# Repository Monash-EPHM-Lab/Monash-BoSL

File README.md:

# Monash-BoSL
Monash-BoSL project repository

This repostory contains all the hardware and software resources for the BoSL board.

Find our website at: www.bosl.com.au

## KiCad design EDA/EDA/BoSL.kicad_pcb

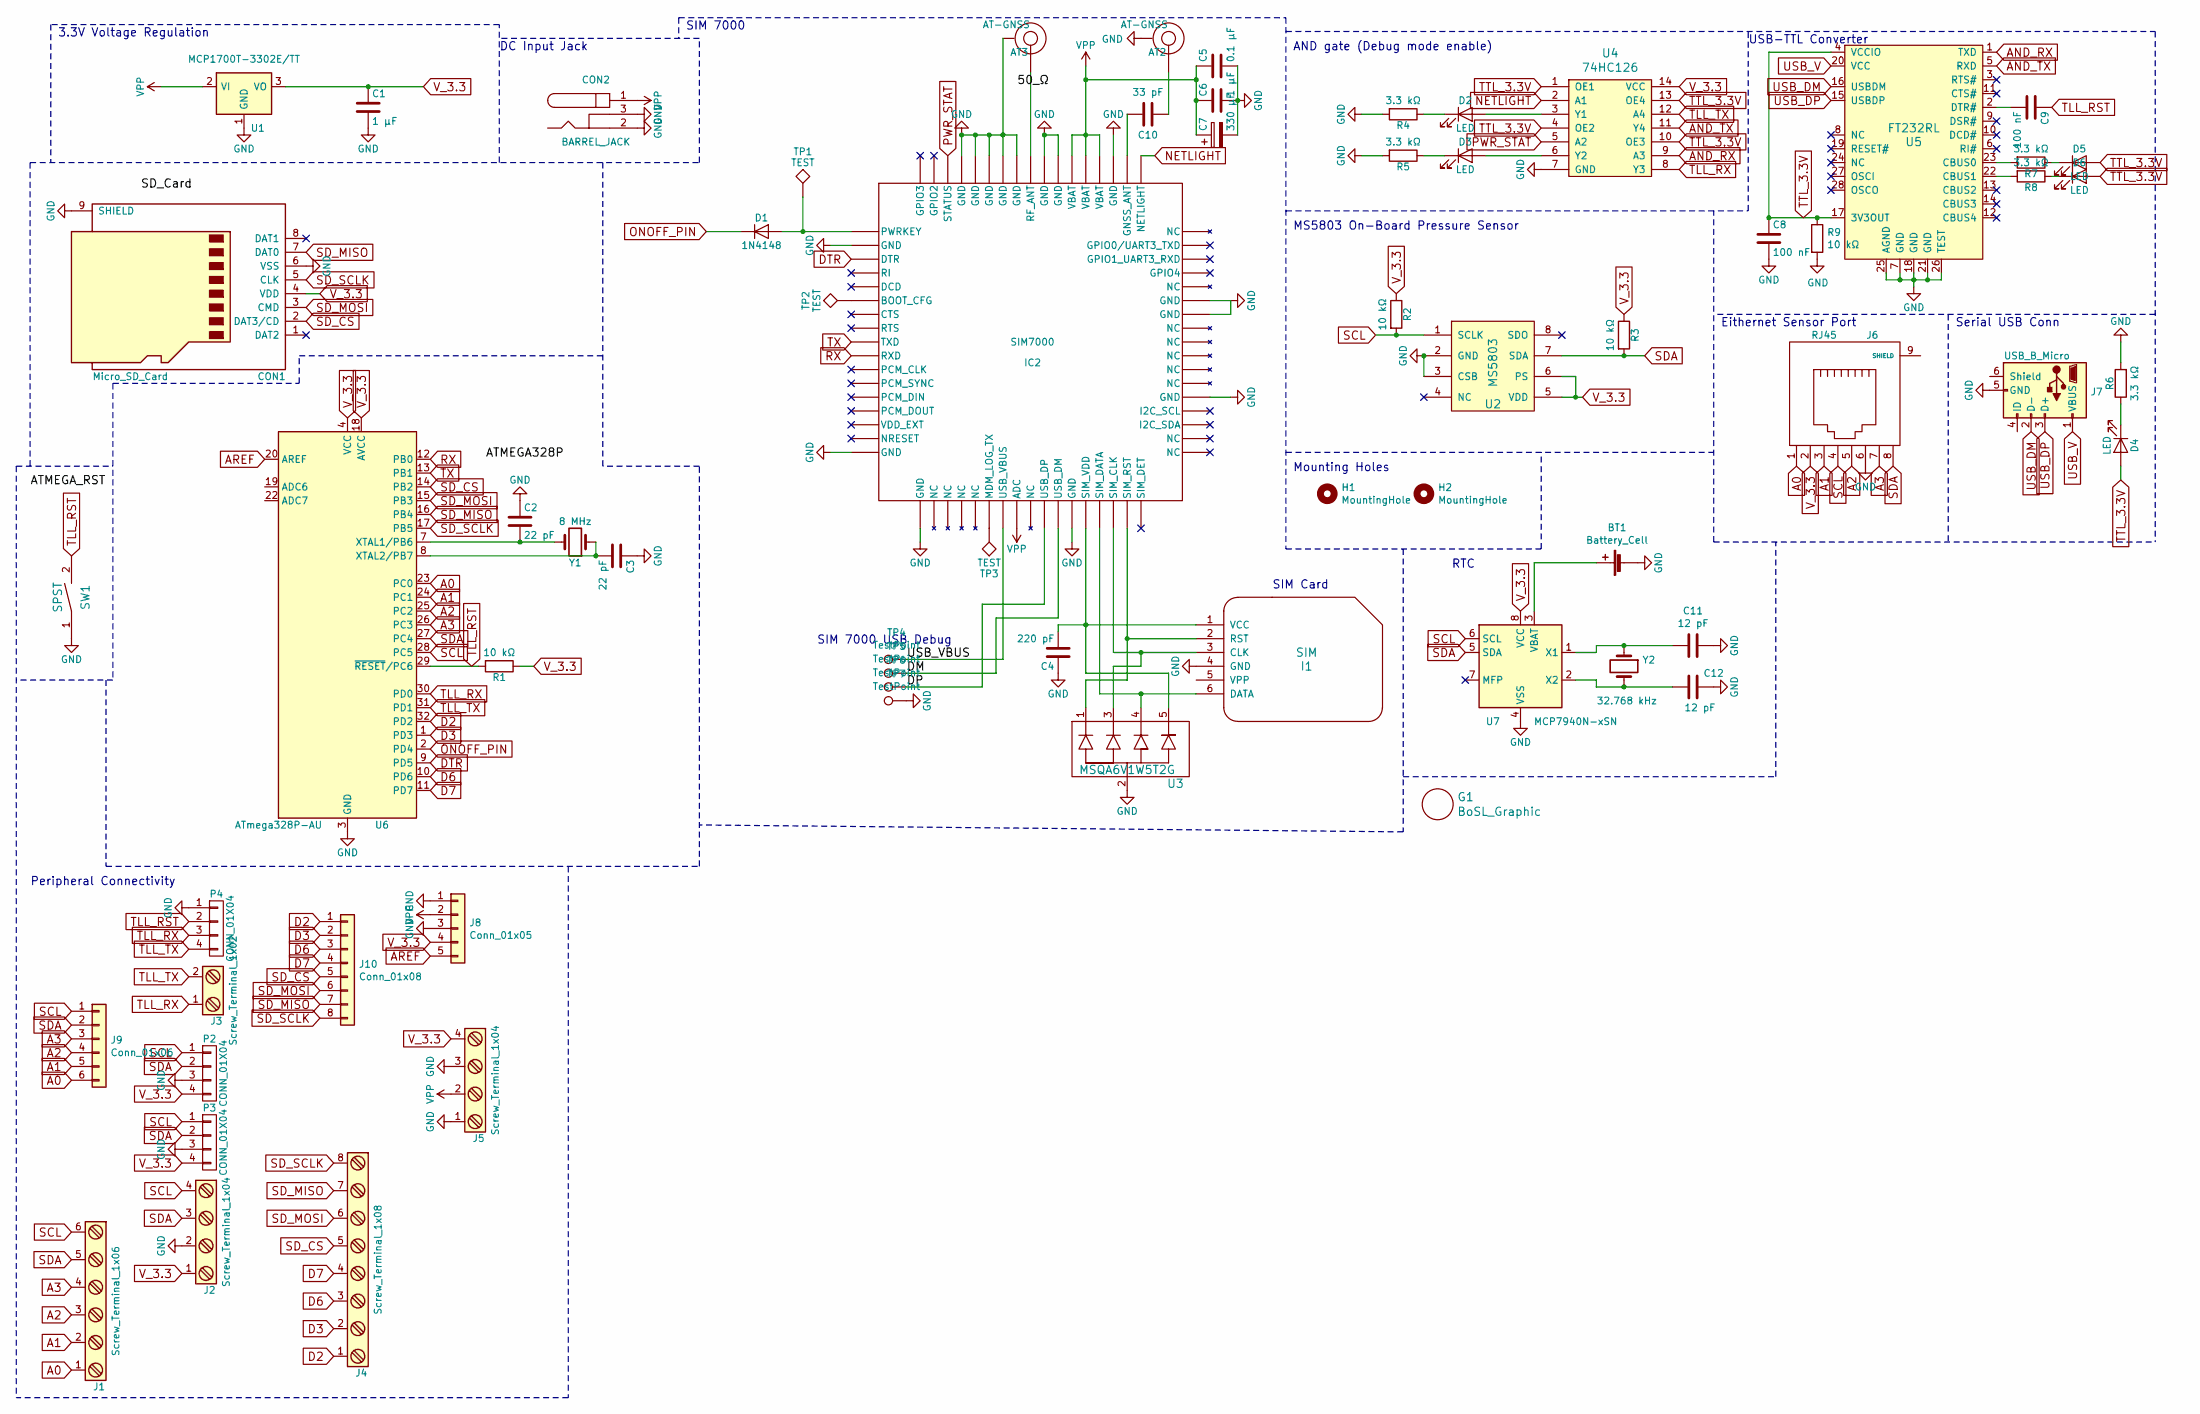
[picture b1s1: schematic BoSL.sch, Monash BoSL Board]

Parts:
AT2, AT3: AT-GNSS; U.FL_Molex_MCRF_73412-0110_Vertical
BT1: Battery_Cell; 2996TR
C1, C6: 1 μF; C_1206_3216Metric
C2, C3: 22 pF; C_0805_2012Metric
C4: 220 pF; C_0805_2012Metric
C5: 0.1 μF; C_0805_2012Metric
C7: 330 μF; CP_Elec_8x10
C8, C9: 100 nF; C_0805_2012Metric
C10: 33 pF; C_0805_2012Metric
C11, C12: 12 pF; C_0805_2012Metric
CON1: Micro_SD_Card; microSD_Connector
CON2: BARREL_JACK; BarrelJack_Horizontal
D1: 1N4148; D_SOD-323
D2, D3, D4, D5, D6: LED; LED_0805_2012Metric
G1: BoSL_Graphic
H1, H2: MountingHole; MountingHole_2.2mm_M2_Pad
I1: SIM; SIMNano
IC2: SIM7000
J1: Screw_Terminal_1x06; TerminalBlock_Phoenix_PT-1,5-6-3.5-H_1x06_P3.50mm_Horizontal
J2, J5: Screw_Terminal_1x04; TerminalBlock_Phoenix_PT-1,5-4-3.5-H_1x04_P3.50mm_Horizontal
J3: Screw_Terminal_1x02; TerminalBlock_Phoenix_PT-1,5-2-3.5-H_1x02_P3.50mm_Horizontal
J4: Screw_Terminal_1x08; TerminalBlock_Phoenix_PT-1,5-8-3.5-H_1x08_P3.50mm_Horizontal
J6: RJ45; RJ_45
J7: USB_B_Micro; USB_Micro-B_Molex-105133-0001
J8: Conn_01x05; PinHeader_1x05_P2.54mm_Vertical
J9: Conn_01x06; PinHeader_1x06_P2.54mm_Vertical
J10: Conn_01x08; PinHeader_1x08_P2.54mm_Vertical
P2, P3, P4: CONN_01X04; PinHeader_1x04_P2.54mm_Vertical
R1, R2, R3, R9: 10 kΩ; R_0805_2012Metric
R4, R5, R6, R7, R8: 3.3 kΩ; R_0805_2012Metric
SW1: SPST; SW_SPST_B3S-1000
TP1, TP2, TP3: TEST; TestPoint_Pad_D1.0mm
TP4, TP5, TP6, TP7: TestPoint; TestPoint_Pad_1.5x1.5mm
U1: MCP1700T-3302E/TT; SOT-89-3
U2: MS5803
U3: MSQA6V1W5T2G; SOT-353_SC-70-5
U4: 74HC126; SOIC-14_3.9x8.7mm_P1.27mm
U5: FT232RL; SSOP-28_5.3x10.2mm_P0.65mm
U6: ATmega328P-AU; TQFP-32_7x7mm_P0.8mm
U7: MCP7940N-xSN; SOIC-8_3.9x4.9mm_P1.27mm
Y1: 8 MHz; Crystal_SMD_5032-2Pin_5.0x3.2mm
Y2: 32.768 kHz; Crystal_SMD_EuroQuartz_EQ161-2Pin_3.2x1.5mm

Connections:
/DM: IC2.28 (USB_DM), TP5.1
/DP: IC2.27 (USB_DP), TP6.1
/USB_VBUS: IC2.24 (USB_VBUS), TP4.1
A0: J1.1, J6.1, J9.6, U6.23 (PC0)
A1: J1.2, J6.3, J9.5, U6.24 (PC1)
A2: J1.3, J6.5, J9.4, U6.25 (PC2)
A3: J1.4, J6.7, J9.3, U6.26 (PC3)
AND_RX: U4.9 (A3), U5.1 (TXD)
AND_TX: U4.11 (Y4), U5.5 (RXD)
AREF: J8.5, U6.20 (AREF)
D2: J4.1, J10.1, U6.32 (PD2)
D3: J4.2, J10.2, U6.1 (PD3)
D6: J4.3, J10.3, U6.10 (PD6)
D7: J4.4, J10.4, U6.11 (PD7)
DTR: IC2.3 (DTR), U6.9 (PD5)
GND: AT2.2, AT3.2, BT1.2 (-), C1.2, C2.1, C3.1, C4.1, C5.2, C6.2, C7.2, C8.2, C11.1, C12.1, CON1.6 (VSS), CON1.9 (SHIELD), CON2.2, CON2.3, I1.4 (GND), IC2.2 (GND), IC2.17 (GND), IC2.18 (GND), IC2.29 (GND), IC2.39 (GND), IC2.45 (GND), IC2.46 (GND), IC2.54 (GND), IC2.58 (GND), IC2.59 (GND), IC2.61 (GND), IC2.62 (GND), IC2.63 (GND), IC2.64 (GND), IC2.65 (GND), J2.2, J5.1, J5.3, J6.6, J7.5 (GND), J8.1, J8.3, P2.3, P3.3, P4.1, R4.2, R5.2, R6.2, R9.2, SW1.1, TP7.1, U1.1 (GND), U2.2 (GND), U2.3 (CSB), U3.2, U4.7 (GND), U5.7 (GND), U5.18 (GND), U5.21 (GND), U5.25 (AGND), U5.26 (TEST), U6.3 (GND), U6.5 (GND), U6.21 (GND), U7.4 (VSS)
NETLIGHT: IC2.52 (NETLIGHT), U4.2 (A1)
unnamed: AT2.1, C10.1
unnamed: AT3.1, IC2.60 (RF_ANT)
unnamed: BT1.1 (+), U7.3 (VBAT)
unnamed: C2.2, U6.7 (XTAL1/PB6), Y1.2
unnamed: C3.2, U6.8 (XTAL2/PB7), Y1.1
unnamed: C4.2, I1.1 (VCC), IC2.30 (SIM_VDD), U3.5
unnamed: C9.2, U5.2 (DTR#)
unnamed: C10.2, IC2.53 (GNSS_ANT)
unnamed: C11.2, U7.1 (X1), Y2.1
unnamed: C12.2, U7.2 (X2), Y2.2
unnamed: D1.2 (A), IC2.1 (PWRKEY), TP1.1
unnamed: D2.1 (K), R4.1
unnamed: D2.2 (A), U4.3 (Y1)
unnamed: D3.1 (K), R5.1
unnamed: D3.2 (A), U4.6 (Y2)
unnamed: D4.1 (K), R6.1
unnamed: D5.1 (K), R7.1
unnamed: D6.1 (K), R8.1
unnamed: I1.2 (RST), IC2.33 (SIM_RST), U3.1
unnamed: I1.3 (CLK), IC2.32 (SIM_CLK), U3.3
unnamed: I1.6 (DATA), IC2.31 (SIM_DATA), U3.4
unnamed: IC2.6 (BOOT_CFG), TP2.1
unnamed: IC2.23 (MDM_LOG_TX), TP3.1
unnamed: R7.2, U5.23 (CBUS0)
unnamed: R8.2, U5.22 (CBUS1)
ONOFF_PIN: D1.1 (K), U6.2 (PD4)
PWR_STAT: IC2.66 (STATUS), U4.5 (A2)
RX: IC2.10 (RXD), U6.12 (PB0)
SCL: J1.6, J2.4, J6.4, J9.1, P2.1, P3.1, R2.2, U2.1 (SCLK), U6.28 (PC5), U7.6 (SCL)
SDA: J1.5, J2.3, J6.8, J9.2, P2.2, P3.2, R3.2, U2.7 (SDA), U6.27 (PC4), U7.5 (SDA)
SD_CS: CON1.2 (DAT3/CD), J4.5, J10.5, U6.14 (PB2)
SD_MISO: CON1.7 (DAT0), J4.7, J10.7, U6.16 (PB4)
SD_MOSI: CON1.3 (CMD), J4.6, J10.6, U6.15 (PB3)
SD_SCLK: CON1.5 (CLK), J4.8, J10.8, U6.17 (PB5)
TLL_RST: C9.1, P4.2, R1.2, SW1.2, U6.29 (~RESET~/PC6)
TLL_RX: J3.1, P4.3, U4.8 (Y3), U6.30 (PD0)
TLL_TX: J3.2, P4.4, U4.12 (A4), U6.31 (PD1)
TTL_3.3V: C8.1, D4.2 (A), D5.2 (A), D6.2 (A), R9.1, U4.1 (OE1), U4.4 (OE2), U4.10 (OE3), U4.13 (OE4), U5.4 (VCCIO), U5.17 (3V3OUT)
TX: IC2.9 (TXD), U6.13 (PB1)
USB_DM: J7.2 (D-), U5.16 (USBDM)
USB_DP: J7.3 (D+), U5.15 (USBDP)
USB_V: J7.1 (VBUS), U5.20 (VCC)
VPP: C5.1, C6.1, C7.1, CON2.1, IC2.25 (ADC), IC2.55 (VBAT), IC2.56 (VBAT), IC2.57 (VBAT), J5.2, J8.2, U1.2 (VI)
V_3.3: C1.1, CON1.4 (VDD), J2.1, J5.4, J6.2, J8.4, P2.4, P3.4, R1.1, R2.1, R3.1, U1.3 (VO), U2.5 (VDD), U2.6 (PS), U4.14 (VCC), U6.4 (VCC), U6.6 (VCC), U6.18 (AVCC), U7.8 (VCC)

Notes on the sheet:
3.3V Voltage Regulation
DC Input Jack
SIM 7000
SIM Card
SIM 7000 USB Debug
AND gate (Debug mode enable)
USB-TTL Converter
Serial USB Conn
Eithernet Sensor Port
MS5803 On-Board Pressure Sensor
Peripheral Connectivity
Mounting Holes
RTC

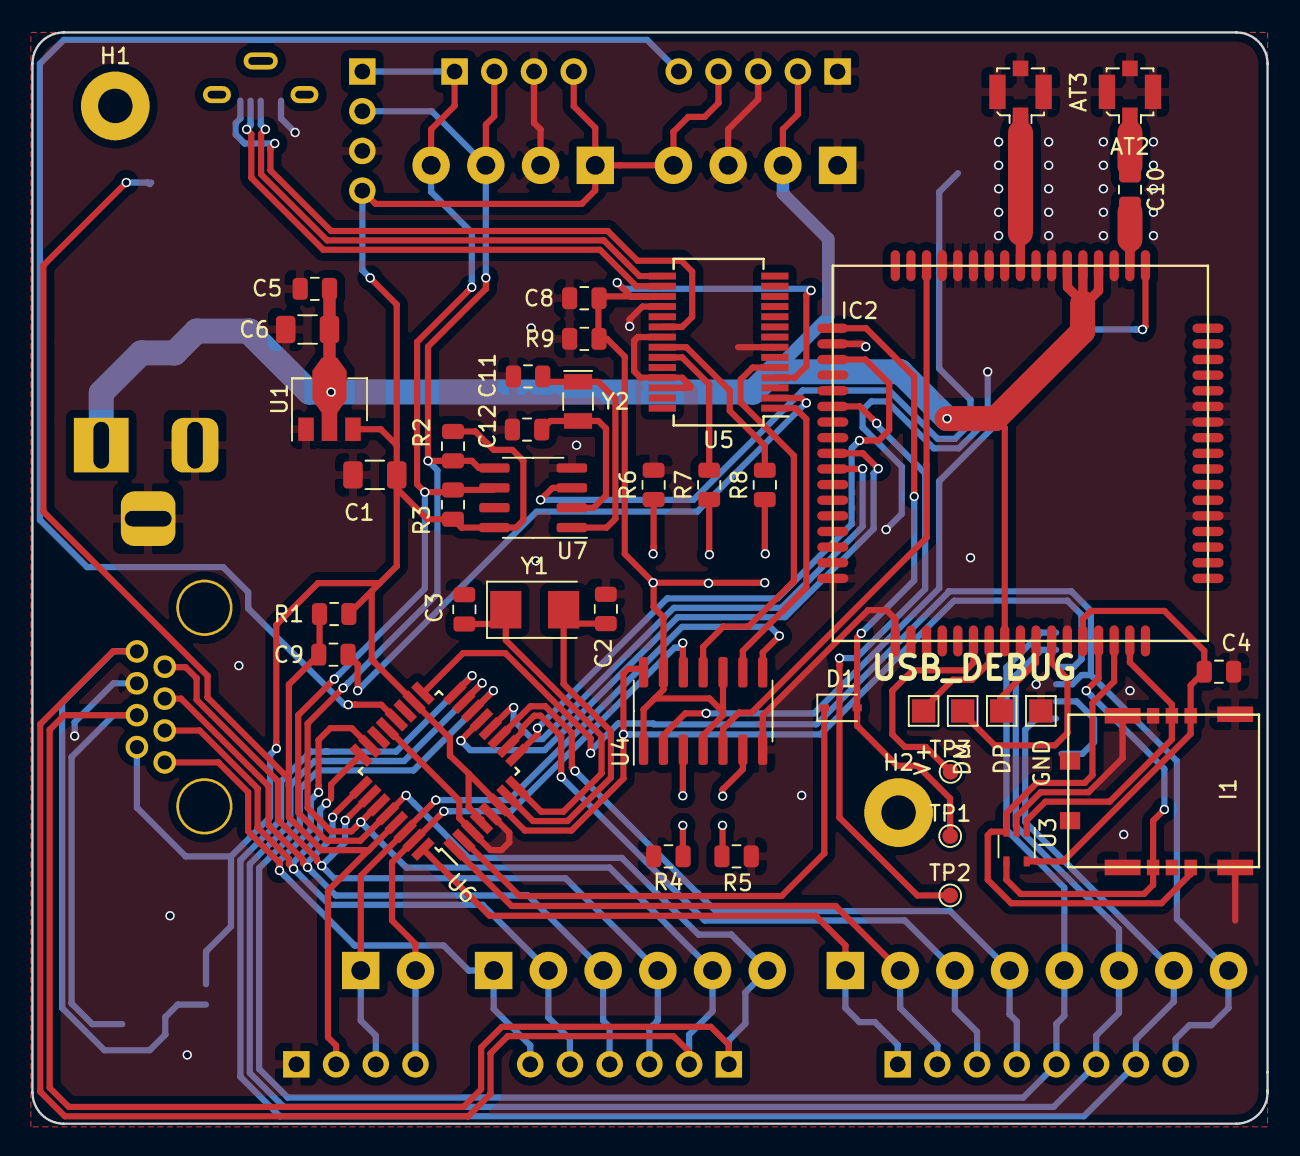
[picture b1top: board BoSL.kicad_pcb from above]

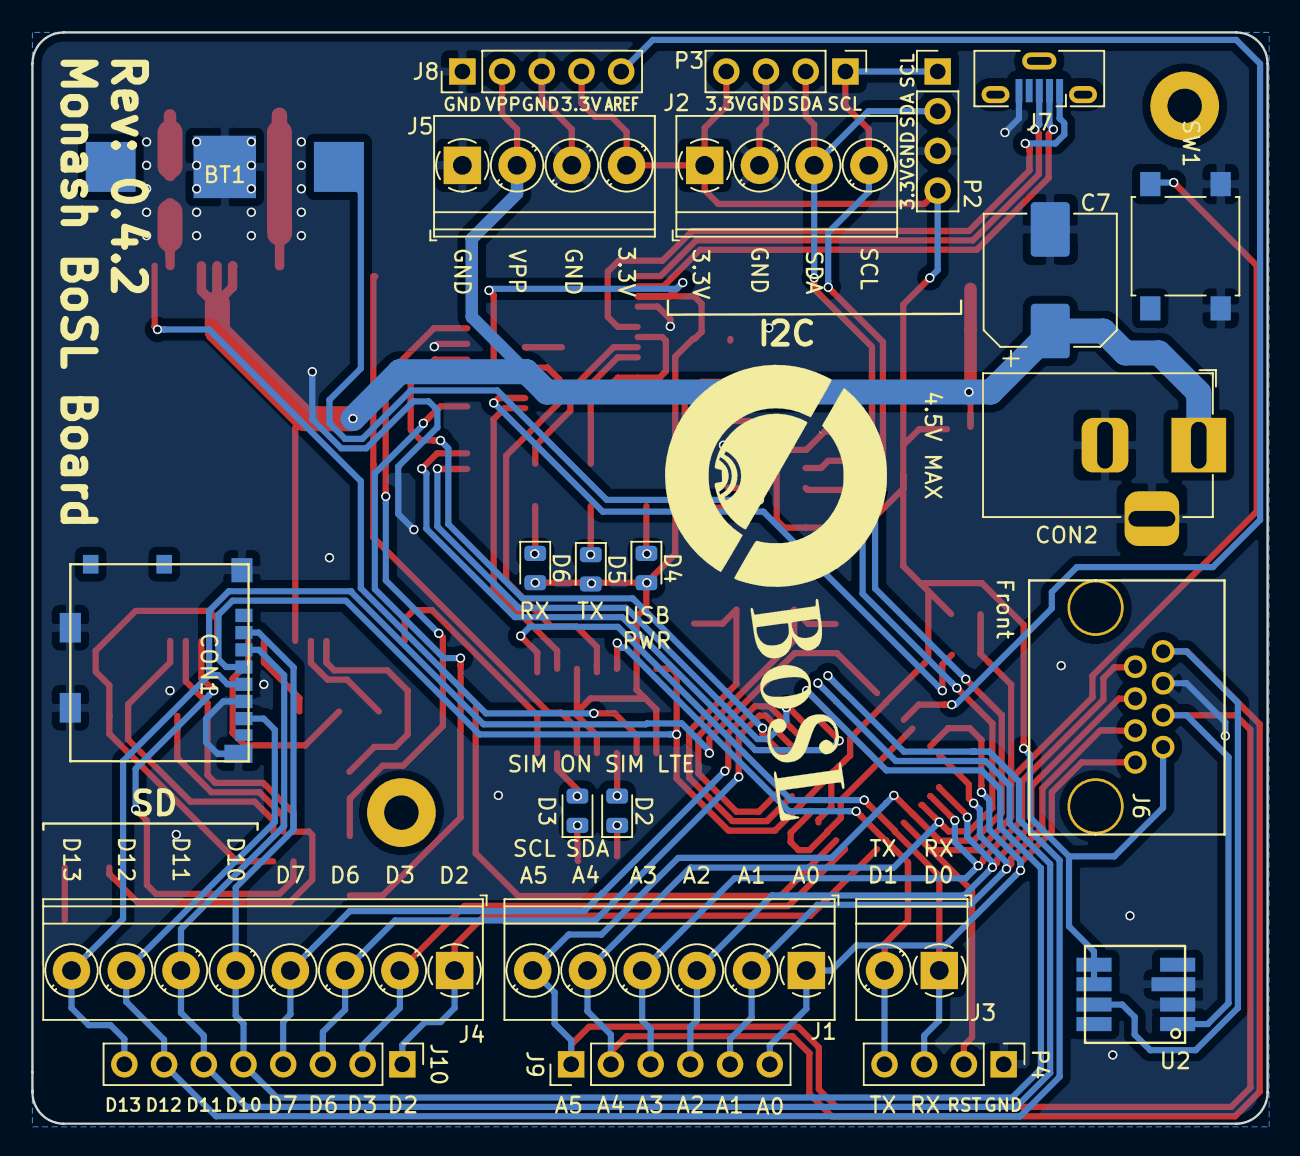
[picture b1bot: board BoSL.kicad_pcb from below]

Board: 2 copper layers, 79.0 x 69.8 mm, 67 parts (25 on the bottom side), 61 nets.

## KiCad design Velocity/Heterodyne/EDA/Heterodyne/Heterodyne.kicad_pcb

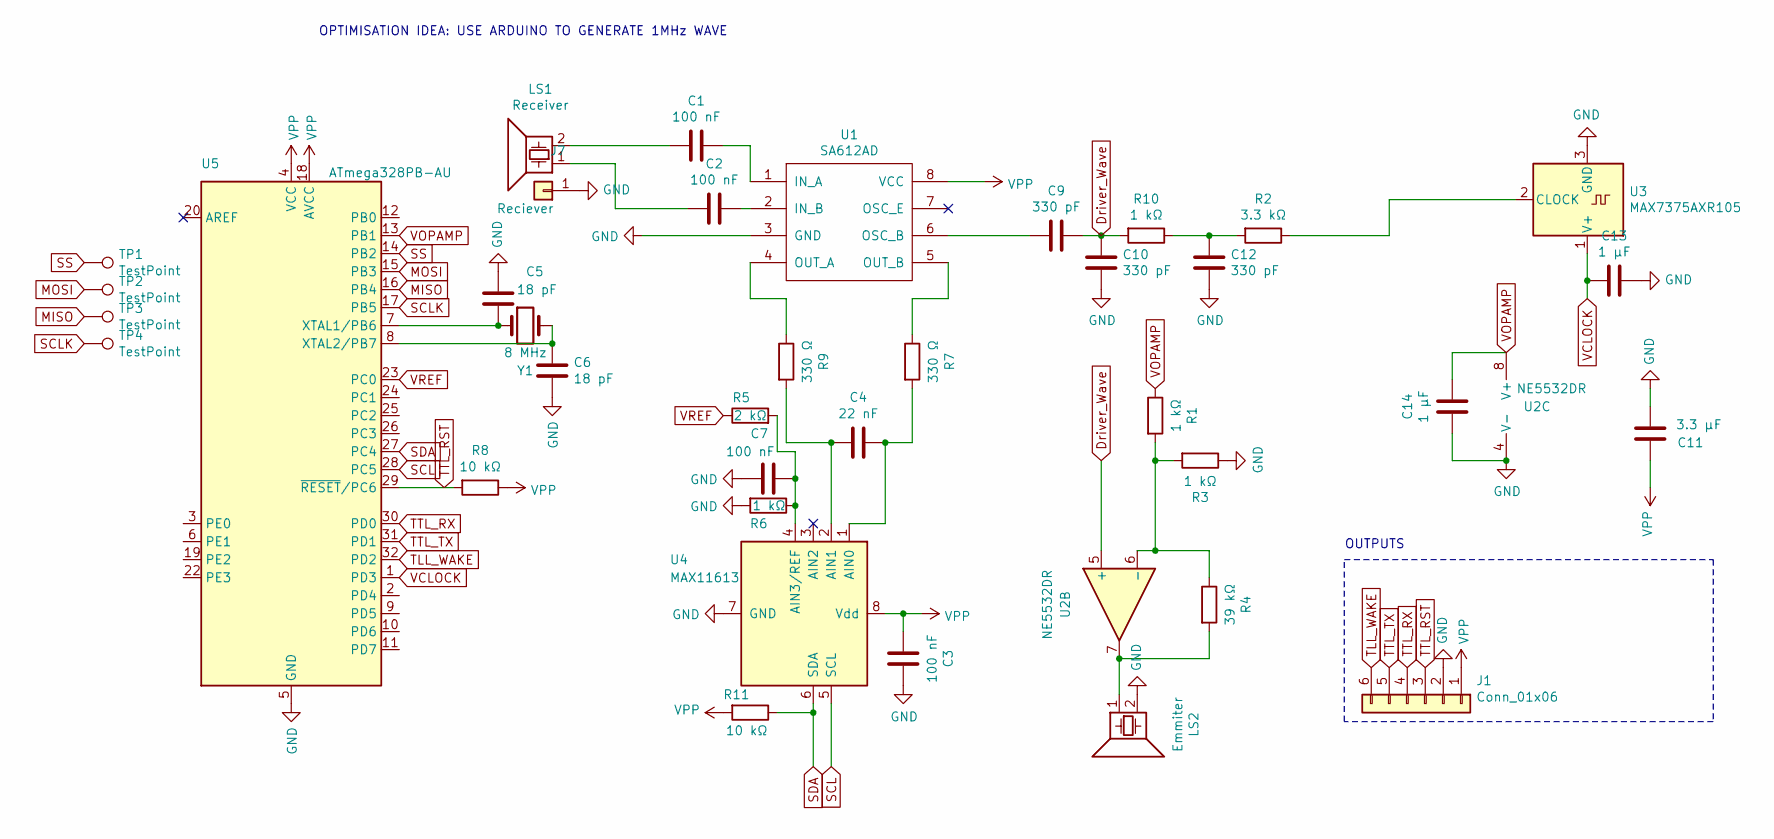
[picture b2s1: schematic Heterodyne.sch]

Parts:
C1, C2, C3, C7: 100 nF; C_0603_1608Metric_Pad1.05x0.95mm_HandSolder
C4: 22 nF; C_0603_1608Metric_Pad1.05x0.95mm_HandSolder
C5, C6: 18 pF; C_0603_1608Metric_Pad1.05x0.95mm_HandSolder
C9, C10, C12: 330 pF; C_0603_1608Metric_Pad1.05x0.95mm_HandSolder
C11: 3.3 μF; C_0805_2012Metric
C13, C14: 1 μF; C_0805_2012Metric
J1: Conn_01x06; PinHeader_1x06_P2.54mm_Vertical
J7: Reciever; PinSocket_1x01_P2.54mm_Vertical
LS1: Receiver; PinHeader_1x02_P2.54mm_Vertical
LS2: Emmiter; PinHeader_1x02_P2.54mm_Vertical
R1, R3, R6, R10: 1 kΩ; R_0603_1608Metric_Pad1.05x0.95mm_HandSolder
R2: 3.3 kΩ; R_0603_1608Metric_Pad1.05x0.95mm_HandSolder
R4: 39 kΩ; R_0603_1608Metric_Pad1.05x0.95mm_HandSolder
R5: 2 kΩ; R_0603_1608Metric_Pad1.05x0.95mm_HandSolder
R7, R9: 330 Ω; R_0603_1608Metric_Pad1.05x0.95mm_HandSolder
R8, R11: 10 kΩ; R_0603_1608Metric_Pad1.05x0.95mm_HandSolder
TP1, TP2, TP3, TP4: TestPoint; Testpoint SPI
U1: SA612AD; SOIC-8_5.275x5.275mm_P1.27mm
U2: NE5532DR; SOIC-8_3.9x4.9mm_P1.27mm
U3: MAX7375AXR105; SOT-323_SC-70_Handsoldering
U4: MAX11613; MSOP-8_3x3mm_P0.65mm
U5: ATmega328PB-AU; TQFP-32_7x7mm_P0.8mm
Y1: 8 MHz; Crystal_SMD_5032-2Pin_5.0x3.2mm

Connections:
Driver_Wave: C9.1, C10.2, R10.2, U2.5 (+)
GND: C3.1, C5.1, C6.2, C7.2, C10.1, C11.2, C12.2, C13.1, C14.2, J1.2, J7.1, LS2.2, R3.1, R6.2, U1.3 (GND), U2.4 (V-), U3.3 (GND), U4.7 (GND), U5.5 (GND), U5.21 (GND)
MISO: TP3.1, U5.16 (PB4)
MOSI: TP2.1, U5.15 (PB3)
unnamed: C1.1, U1.1 (IN_A)
unnamed: C1.2, LS1.2
unnamed: C2.1, U1.2 (IN_B)
unnamed: C2.2, LS1.1
unnamed: C4.1, R7.2, U4.1 (AIN0)
unnamed: C4.2, R9.2, U4.2 (AIN1)
unnamed: C5.2, U5.7 (XTAL1/PB6), Y1.1
unnamed: C6.1, U5.8 (XTAL2/PB7), Y1.2
unnamed: C7.1, R5.2, R6.1, U4.4 (AIN3/REF)
unnamed: C9.2, U1.6 (OSC_B)
unnamed: C12.1, R2.2, R10.1
unnamed: LS2.1, R4.2, U2.7
unnamed: R1.2, R3.2, R4.1, U2.6 (-)
unnamed: R2.1, U3.2 (CLOCK)
unnamed: R7.1, U1.5 (OUT_B)
unnamed: R9.1, U1.4 (OUT_A)
SCL: U4.5 (SCL), U5.28 (PC5)
SCLK: TP4.1, U5.17 (PB5)
SDA: R11.1, U4.6 (SDA), U5.27 (PC4)
SS: TP1.1, U5.14 (PB2)
TLL_WAKE: J1.6, U5.32 (PD2)
TTL_RST: J1.3, R8.2, U5.29 (~RESET~/PC6)
TTL_RX: J1.4, U5.30 (PD0)
TTL_TX: J1.5, U5.31 (PD1)
VCLOCK: C13.2, U3.1 (V+), U5.1 (PD3)
VOPAMP: C14.1, R1.1, U2.8 (V+), U5.13 (PB1)
VPP: C3.2, C11.1, J1.1, R8.1, R11.2, U1.8 (VCC), U4.8 (Vdd), U5.4 (VCC), U5.18 (AVCC)
VREF: R5.1, U5.23 (PC0)

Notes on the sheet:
OUTPUTS
OPTIMISATION IDEA: USE ARDUINO TO GENERATE 1MHz WAVE

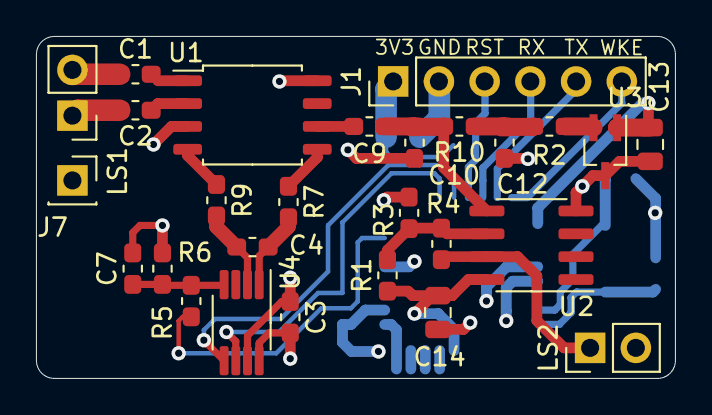
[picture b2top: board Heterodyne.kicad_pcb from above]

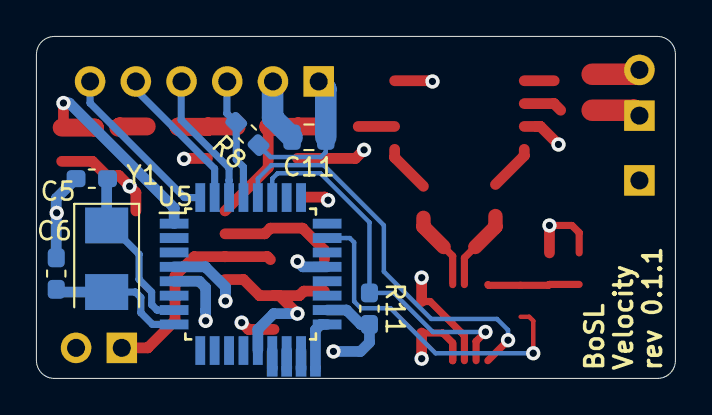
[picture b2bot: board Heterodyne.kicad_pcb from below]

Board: 4 copper layers, 35.5 x 19.0 mm, 38 parts (11 on the bottom side), 32 nets.

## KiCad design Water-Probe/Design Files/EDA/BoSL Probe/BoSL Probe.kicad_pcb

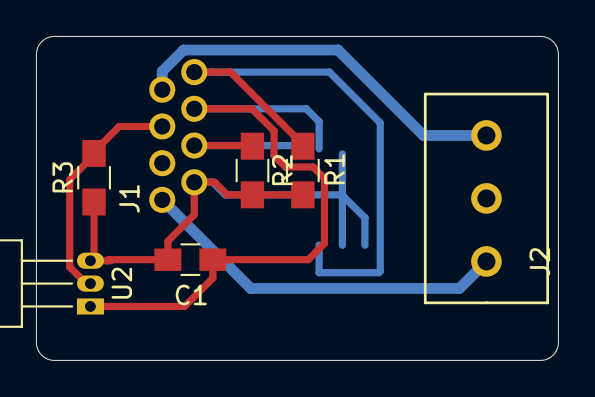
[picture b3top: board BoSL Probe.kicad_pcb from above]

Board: 2 copper layers, 29.0 x 18.0 mm, 8 parts (1 on the bottom side), 7 nets.

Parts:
C1: 100nF; C_0805_HandSoldering
J1: 8P8C_Shielded; RJ_45
J2: Screw_Terminal_01x03; Screw_Terminals_1x3_3.5mm
R1, R2: 10 kΩ; R_0805_HandSoldering
R3: 4.7 kΩ; R_0805_HandSoldering
U1: MS5803-01BA; MS5803
U2: DS18B20; TO-92_Horizontal2_Inline_Narrow_Oval

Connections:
A0: J1.1, J2.1
A3: J1.7, J2.3
Blue: J1.4, R2.1, U1.1
BlueHalf: J1.5, R3.2, U2.2
Brown: J1.8, R1.2, U1.7
Green: C1.2, J1.6, U1.2, U2.1
Orange: C1.1, J1.2, R1.1, R2.2, R3.1, U1.3, U1.5, U1.6, U2.3

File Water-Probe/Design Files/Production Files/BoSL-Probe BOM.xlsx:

Part Number | Package Size / Type | Component | Value | QTY per board | Unit Price | Total Price | Supplier
 | 3 Screw Terminal | Screw Terminal | 3.5mm pitch | 1 | 2.2400000000000002 | 2.2400000000000002 | https://au.element14.com/camdenboss/ctbp3051-3/tb-wire-to-bo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
DS18B20 |  | Temperature Sensor |  | 1 | 4.49 | 4.49 | https://au.element14.com/maxim-integrated-products/ds18b20/t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
MS5803-01BA |  | Pressure / Temperature Sensor |  | 1 | 19 | 19 | https://www.digikey.com/products/es?mpart=MS580301BA01-00&v=223
 | 0805 | Resistor | 10 kΩ | 2 |  | 0
 | 0805 | Resistor | 4.7 kΩ | 1 |  | 0
 | 0805 | Capactor | 100 nF | 1 |  | 0
 |  | Metal Cap |  | 1
 |  | Stainless Steel Dowel Pin | 35 mm Length 1/16" dia | 2 |  | 0
 |  | Eithernet Cable | 2.5 m | 1 |  | 0

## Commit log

2019-04-03 Organised arduino files so can be uploaded to arduino
2019-04-04 Modified Aruino code to upload battery data once an hour
2019-04-04 Daily Commit
2019-04-05 Cleaned up files structure
2019-04-05 Uploaded code files
2019-04-05 Added tasklist
2019-04-08 Final Code to be uploaded
2019-04-11 updated tasklist
2019-04-11 Orginal Code release
2019-04-11 Updated tasklist to be branch specific
2019-04-11 Push of folder structure for development
2019-04-11 Began Cleaning up code Added begginings of classes for future implementation
2019-04-11 daily push
2019-05-01 Add files via upload
    Code that fixed EC corrosion issues
2019-05-01 Switched power pins of ec from analogue to ground
2019-05-01 push prior to ec debug, implemented ec polarity switching
2019-05-02 Added compensation for polarity swiching ec value changes
2019-05-02 realease candiate for polarity switching on EC, code to be tested in lab
2019-05-02 Added EC test
2019-05-02 file structure cleanup
2019-05-02 arrays created in SensorData library
2019-05-16 added lib files which belong in Arduino libraries folder.
2019-05-16 added ec library
2019-05-16 tested EC libary, ready for implementation into long term test
2019-05-16 added print method on sensor data class
2019-05-22 updated sensor data to print transmited values
2019-05-23 made some improvements and additions. Need to lab test EC sensor
2019-05-23 further modifications made to EC averaging
2019-05-23 moved SIM7000 code into main EoDCLib folder. Further improvements and methods to EC
2019-06-13 updated plan
2019-06-15 reworked sensordata arrays and added saving. not tested yet
2019-06-16 implemented getting data back from array
2019-06-16 began work on new EoDC main ino file with new functionality
2019-06-20 fixed sprintf float bug
2019-06-20 final commit before starting EEPROM version
2019-07-18 modified EC to return resistance on probe conducivity is probe specific and would need to be calibrated calibration values added suggested calibration method: - short probe and adjust Rcable untill g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
2019-07-21 manually merged changes from SDCard EC
2019-07-21 Resolved merge conflicts manually
2019-07-21 renamed messy merge files
2019-07-22 Calibrated EC with lab measured samples
2019-07-23 calibrated EC sensors
2019-07-23 added fixes for v0.2
2019-07-27 updated sim7000.cpp
2019-08-10 changed folder structure
2019-08-12 simplifying class structure
2019-08-14 added low current measured (in other script) sleep mode
2019-08-15 tested version working with BoSL board v0.1
2019-08-15 updated Serial port logging information
2019-08-16 fixed to power testing
2019-08-23 tested version on v0.2
2019-08-26 sitename change
2019-09-24 rearrange file structure
2019-09-24 rearranging files
2019-09-24 rearranging folders
2019-09-24 added board and sensor probe files
2019-09-24 remove redundant
2019-09-24 rearranging directories
2019-09-25 fixed mesh of water probe body
2019-09-26 commit before reshaping sensor body to have depth probe at botton
2019-09-26 finished modeling probe shape
2019-09-26 added renderings of probe
2019-09-26 commiting pcb changes for probe
2019-10-03 keystone rightangle screw connectors added
2019-10-03 commit before adding perferations to probe
2019-10-03 added rendering of probe
2019-10-03 added parts list finished rendering dimentions
2019-10-03 cleaned up folder strucutre eg: deleted .DS_store files added power info document for bosl board
2019-10-09 added data point for BoSL battery monitering
2019-10-09 changed ec drum to oval to reduce flow height needed for good ec reading
2019-10-10 adding rev 0.1 of sensor board pcb
2019-10-10 added gcode files for 3d printing of sensor probe
2019-10-10 added pcb renders
2019-10-14 added v8 stl file for water probe body from Dave
2019-10-16 added datapoint for BoSL02 test
2019-10-31 fixed branch commit error
2019-11-01 changed footprint of rj45, courtyard expanded and fixed added bosl GSP version
2019-11-01 generated bosl gsp gerber files and bom
2019-11-13 changed footprints to accomodate part
2019-11-14 daily update
2019-11-15 work on gsp code
2019-11-15 changed probe EC footprint to screw terminal cleaned up bosl GPS code
2019-11-18 transmit code added to gps
2019-11-18 changes, ready for debuging for release
2019-11-19 final revision bosl GPS code
2019-11-19 changed water probe
2019-11-20 added images of sim7000 sim communitcation issue
2019-11-21 SIM7000 sim communication issue report added begun on changes to EC probe body
2019-11-21 added test for probe head and body joint
2019-11-25 fixed water prove head-body joint to fit together when printed added BoSL test script for manufaturing QC added ping feature on bosl GPS to upload ping server when no GPS signal
2019-11-25 fixed bosl gps range threshold
2019-11-25 removed debug lines form bosl gps
2019-11-27 added folder for velocity sensor
2019-11-27 Added AM demodulator Schematic
2019-11-27 added velocity AM demodulator gerbers
2019-11-28 FFT code changed to display speed for head to head tranducers
2019-11-28 Added files for BoSL GPS Micro
2019-11-28 started layout of micro bosl gps
2019-11-29 layout progress of gps micro board
2019-11-29 finished initial layout of BoSL GPS micro
2019-11-29 finished parts list for BoSL GPS Micro
2019-11-29 added bosl probe self test code
2019-12-01 added spi header to bosl GPS micro for bootloading
2019-12-01 added wait period for signal in GNSS code cleaner up some code repetition
2019-12-01 fixed gps code bug, where did not check for fix
2019-12-02 added battery voltage to bosl GPS transmit
2019-12-02 adjusted timings for signal wait on GPS bosl code
2019-12-09 added oscilator for heterodyne circuit
2019-12-10 added bosl velocity 3d caseing
2019-12-11 made changes to bosl probe to improve fit with boards
2019-12-11 added bosl code for bosl probe
2019-12-16 added bom and pcb files for velocity sensor
2019-12-16 added bosllogo to allinone probe
2019-12-17 added links in bosl velocity bom
2019-12-18 added enhanced sleeping code for bosl
2019-12-19 began work on fault tollerant wire library
2019-12-20 added changes to bosl independant code notably created fucntion xDelay which sould be used in place of delay for power optimisations
2019-12-20 impimplemented xdelay and other power optimisation
2019-12-20 EOY commit
2019-12-21 ammened partlist for all-in-one probe
2019-12-30 added display image
2020-01-20 added top/bottom split to all in one probe
2020-01-20 added lip to bottom all in one probe
2020-01-20 all in one probe ready to be printed
2020-01-20 added 3d print files for bosl all in one probe
2020-01-20 added supports for bosl probe casing
2020-01-21 added battery analysis excel spreadsheet for bosl endurance test
2020-01-21 shrunk distance of overhang in bosl all in one casing
2020-01-21 added i2c bus immunity to prevent program from halting when a bad i2c device is plugged in. bosl_independant gives an error message when i2c not functioning correctly or absent
2020-01-22 changed up velocity heterodyne schematic to fix issues with wireing, and so provide a channel for sine wave driver amplification
2020-01-24 added error messages for no sensors on bosl independant added a 100% infull print mode for all-in-one probe
2020-02-04 added updates to heterodyne code to take averages of multiple FFTs changed up heterodyne circuit to fix bugs
2020-02-05 updated data to heterodyne pcb to include adc
2020-02-05 finshsed routing 2 layer board
2020-02-05 calibrated velocity, implemented multi sample rate rangeing
2020-02-07 added velocity testing data
2020-02-10 added code for MAX11645 ADC on velocity
2020-02-10 added differential probing code
2020-02-10 changed heterodyne code to use MAX11645EUA+T heterodyne intervals calibrated
2020-02-11 added dc removal on the FFT for velocity
2020-02-13 added ATmega328P to velocity schematic
2020-02-14 added 4 layer PCB for heterodyne
2020-02-16 added SPI out on velocity ATmega328P
2020-02-20 added two layer version of the Heterodynbe PCB for laser cutting
2020-02-21 added fusion 360 drill files for laser production
2020-02-21 created fusion 360 drill file (external to repository)
2020-02-27 fixed svg files for heterodyne pcb laser manufature
2020-02-27 fixed merge files with master
2020-02-28 added velocity sensor 3d case
2020-02-28 added screw attachement method for two halves of velocity sensor casing
2020-02-28 added modifed designs for laser heterodyne pcb
2020-03-02 added BoSL_Independant_SD card build
2020-03-09 added test for fix fft library
2020-03-09 isolated arduinoFFT library to work on
2020-03-09 added int16_t fft algorithm -implementation tested to have about 15% error from a float implentation -waring! int16_t scales data to get better dynamic range
2020-03-09 added fix fft to heterodyne test file changed i2c library to be able to read more than 255 bytes at a time from device
2020-03-09 increase sample numbers in heterodyne sketch to 256 adjusted all factors to have final number be the same: ToDo: check if the noise floor bin n = 2 is still good with double the samples ToDo: debug a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
2020-03-23 removed bosl velocity laser heterodyne circuit
2020-03-23 organised velocity folder structure
2020-03-24 added velocity casing for smaller tranducer
2020-04-05 added power on lines in heterodyne code for opamp and oscilator
2020-04-06 added i2c address for heterodyne ADC as macro
2020-04-08 fixed code hang in velocity code caused by bad uint8 to uint16 conversion in in i2c library
2020-04-13 switched ADC in velocity sensor from 2 V internal reference to 1V external referecnce in code
2020-04-13 Velocity: changed supply for ADC ref voltage devider from VPP to arduino pin, est current saveings 1 mA
2020-04-13 added STL files for small tranducer case and test holder
2020-04-13 Velocity: 3d print tweek of small tranducer test
2020-04-14 added adjusted small tranducer test for bosl velocity
2020-04-14 velocity: added int16 related fixes for peak finding algorithm.
2020-04-14 Added changes to velocity small tranducer casing based on test fitting and mounting needs for field testing
2020-04-15 tweaked velocity casing
2020-04-15 started work on bosl-bosl velocity interface code
2020-04-16 renamed bosl GPS to bosl
2020-04-16 begun layout of bosl board rev 0.4
2020-04-16 finished bosl board rev0.4 layout
2020-04-17 added bugfixes to bosl-velocity protocal
2020-04-18 added tweaks to velocity sensor casing
2020-04-19 adding bosl bom
2020-04-22 Working velocity code and corresponding bosl upload code
2020-04-22 added velocity case updates
2020-04-24 added update layout for bosl v4
2020-04-27 organised files
2020-04-29 added revision of bosl board
2020-04-30 updated 3d modles for bosl board
2020-05-02 added space savings of BoSL PCB
2020-05-04 updated bosl with small screw terminals
2020-05-04 finished bosl rev0.4
2020-05-08 removed averaging from velocity code
2020-05-11 added dandenong creek velocity testing samples
2020-05-11 changed velocity code to get 3 attempts to get amplitude > 1000
2020-05-11 added updates to peak algorithm on velocity code
2020-08-11 clean for merge
2020-08-11 reorganised files
2020-08-11 branch to develop atmega version of bosl board
2020-10-04 cleaned up legacy files
2020-11-26 added max voltage text to bosl board on input
2021-01-25 added snazy schematic
2021-01-27 changed digital pins on BoSL
